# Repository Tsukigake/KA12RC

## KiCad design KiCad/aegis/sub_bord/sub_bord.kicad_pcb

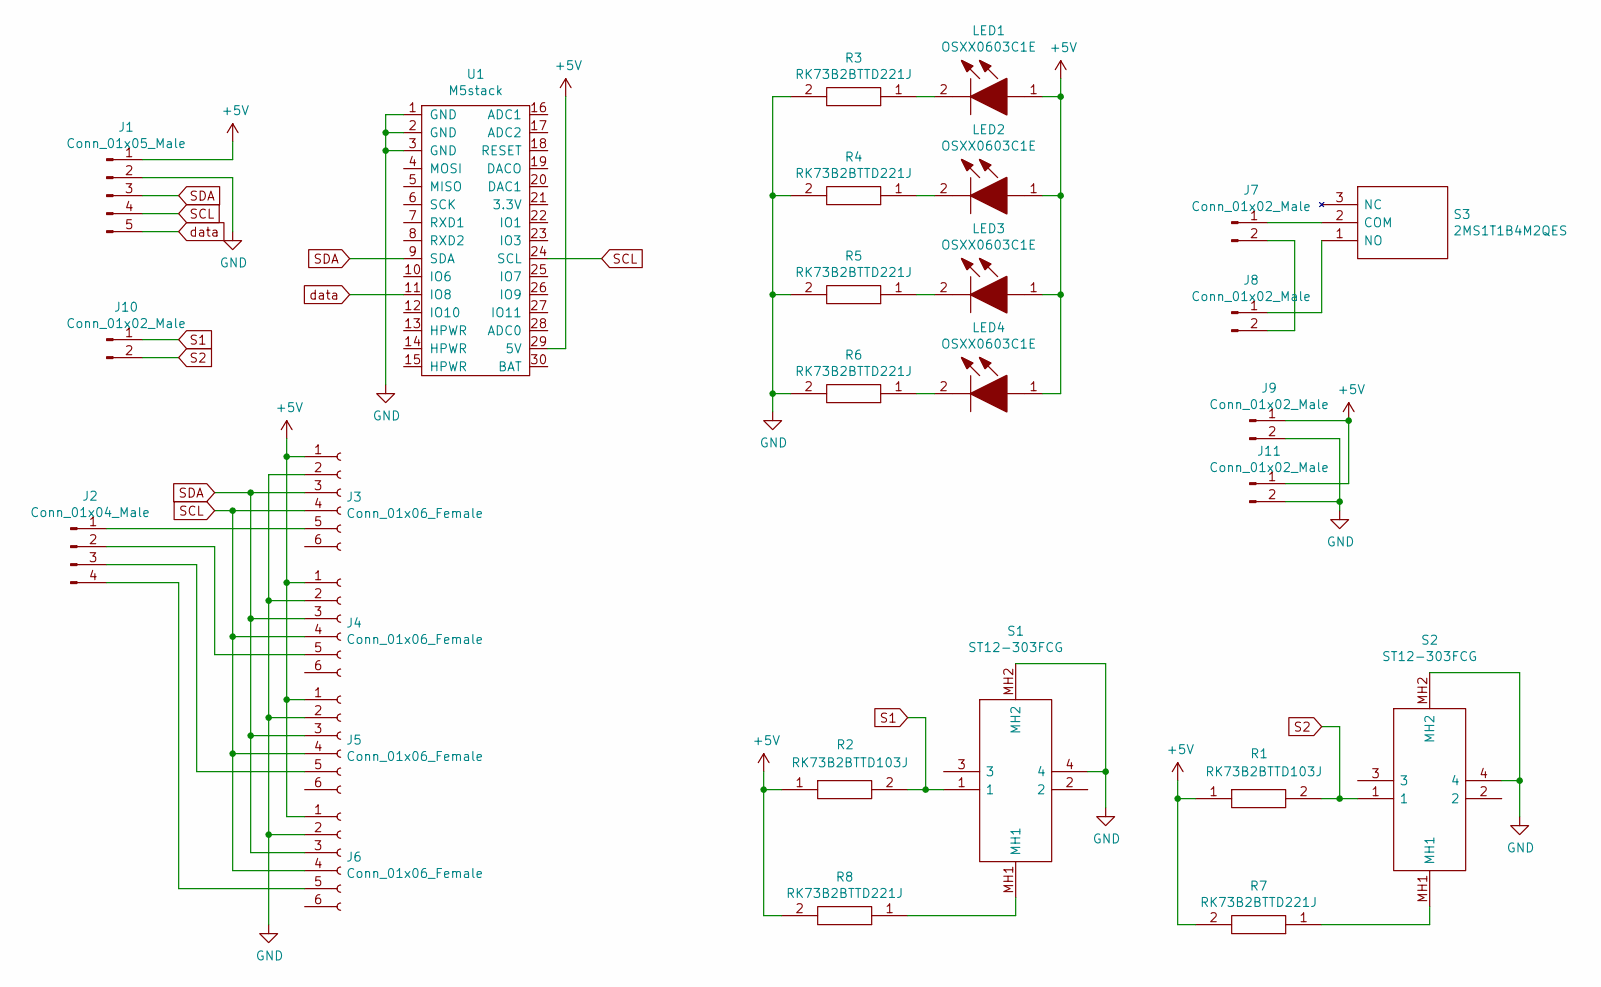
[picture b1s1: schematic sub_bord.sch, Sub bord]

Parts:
J1: Conn_01x05_Male; JST_XH_B5B-XH-A_1x05_P2.50mm_Vertical
J2: Conn_01x04_Male; JST_XH_B4B-XH-A_1x04_P2.50mm_Vertical
J3, J4, J5, J6: Conn_01x06_Female; JST_XH_B6B-XH-A_1x06_P2.50mm_Vertical
J7, J9, J10, J11: Conn_01x02_Male; JST_XH_B2B-XH-A_1x02_P2.50mm_Vertical
J8: Conn_01x02_Male; TerminalBlock_bornier-2_P5.08mm
LED1, LED2, LED3, LED4: OSXX0603C1E; Manufacturer_Part_Number OSXX0603C1E
R1, R2: RK73B2BTTD103J; RESC3216X70N; Manufacturer_Part_Number RK73B2BTTD103J
R3, R4, R5, R6, R7, R8: RK73B2BTTD221J; RESC3216X70N; Manufacturer_Part_Number RK73B2BTTD221J
S1, S2: ST12-303FCG; ST12303FCG; Manufacturer_Part_Number ST12-303FCG
S3: 2MS1T1B4M2QES; Manufacturer_Part_Number 2MS1T1B4M2QES
U1: M5stack

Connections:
+5V: J1.1, J3.1, J4.1, J5.1, J6.1, J9.1, J11.1, LED1.1, LED2.1, LED3.1, LED4.1, R1.1, R2.1, R7.2, R8.2, U1.29 (5V)
GND: J1.2, J3.2, J4.2, J5.2, J6.2, J9.2, J11.2, R3.2, R4.2, R5.2, R6.2, S1.4, S1.MH2, S2.4, S2.MH2, U1.1 (GND), U1.2 (GND), U1.3 (GND)
unnamed: J2.1, J3.5
unnamed: J2.2, J4.5
unnamed: J2.3, J5.5
unnamed: J2.4, J6.5
unnamed: J7.1, S3.2 (COM)
unnamed: J7.2, J8.2
unnamed: J8.1, S3.1 (NO)
unnamed: LED1.2, R3.1
unnamed: LED2.2, R4.1
unnamed: LED3.2, R5.1
unnamed: LED4.2, R6.1
unnamed: R7.1, S2.MH1
unnamed: R8.1, S1.MH1
S1: J10.1, R2.2, S1.1
S2: J10.2, R1.2, S2.1
SCL: J1.4, J3.4, J4.4, J5.4, J6.4, U1.24 (SCL)
SDA: J1.3, J3.3, J4.3, J5.3, J6.3, U1.9 (SDA)
data: J1.5, U1.11 (IO8)

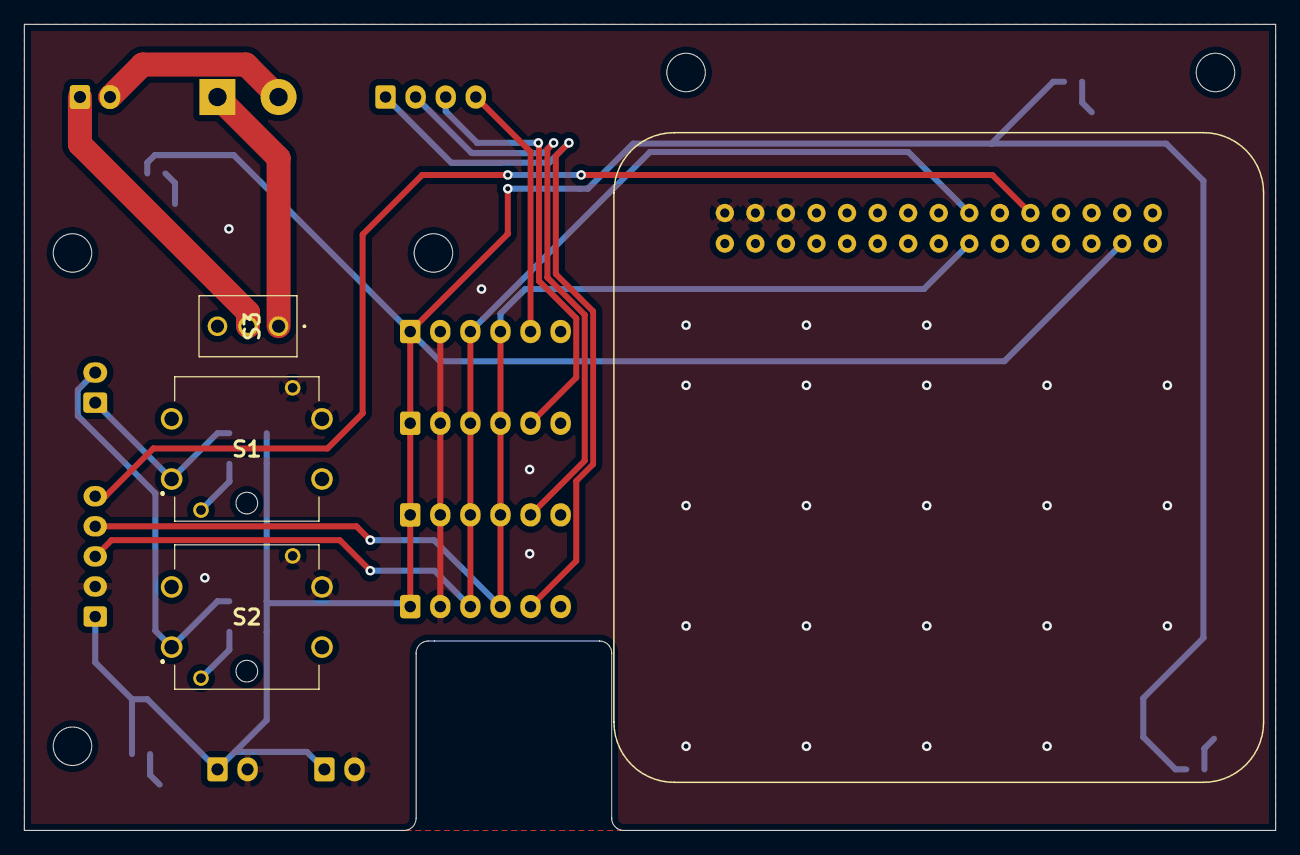
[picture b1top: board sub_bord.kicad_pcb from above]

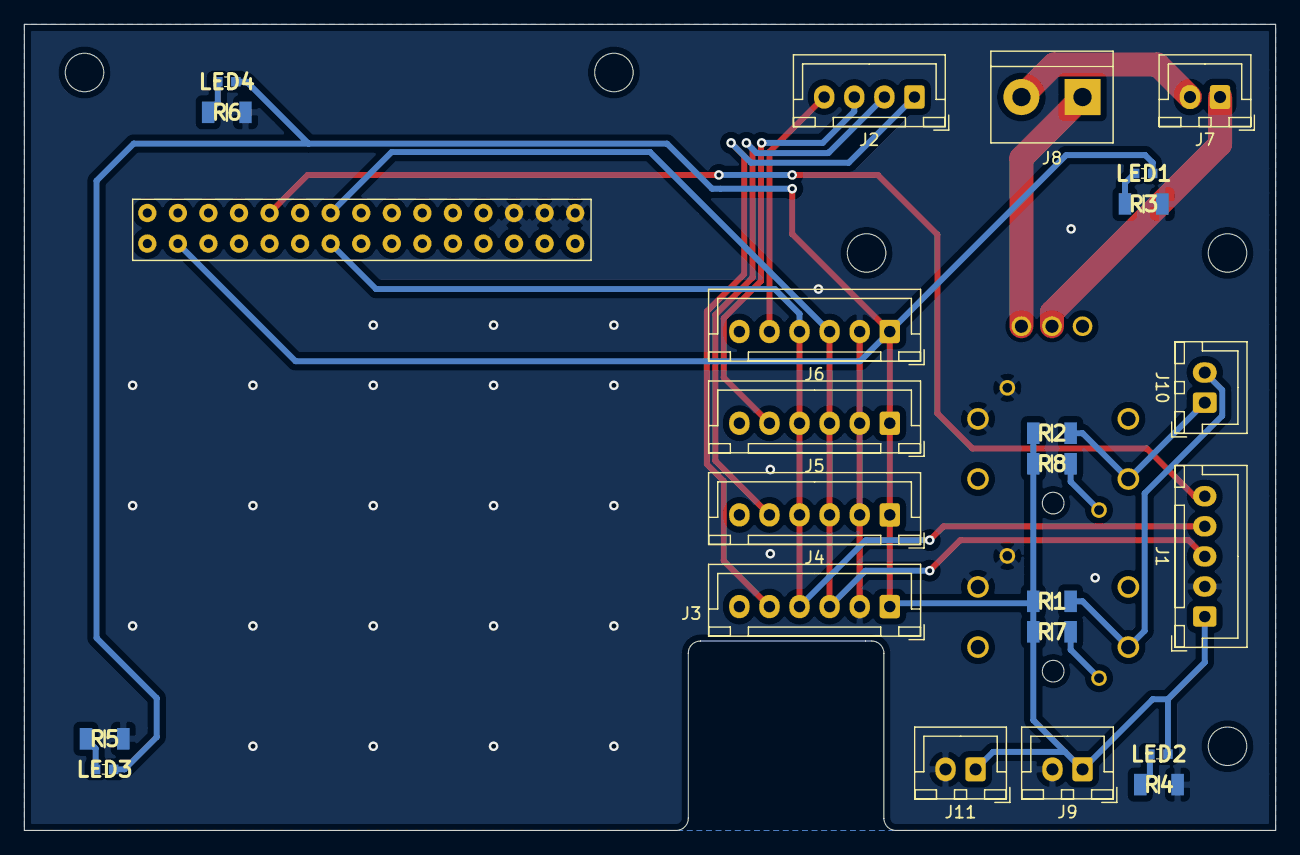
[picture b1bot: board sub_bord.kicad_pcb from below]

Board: 2 copper layers, 104.0 x 67.0 mm, 27 parts (23 on the bottom side), 20 nets.

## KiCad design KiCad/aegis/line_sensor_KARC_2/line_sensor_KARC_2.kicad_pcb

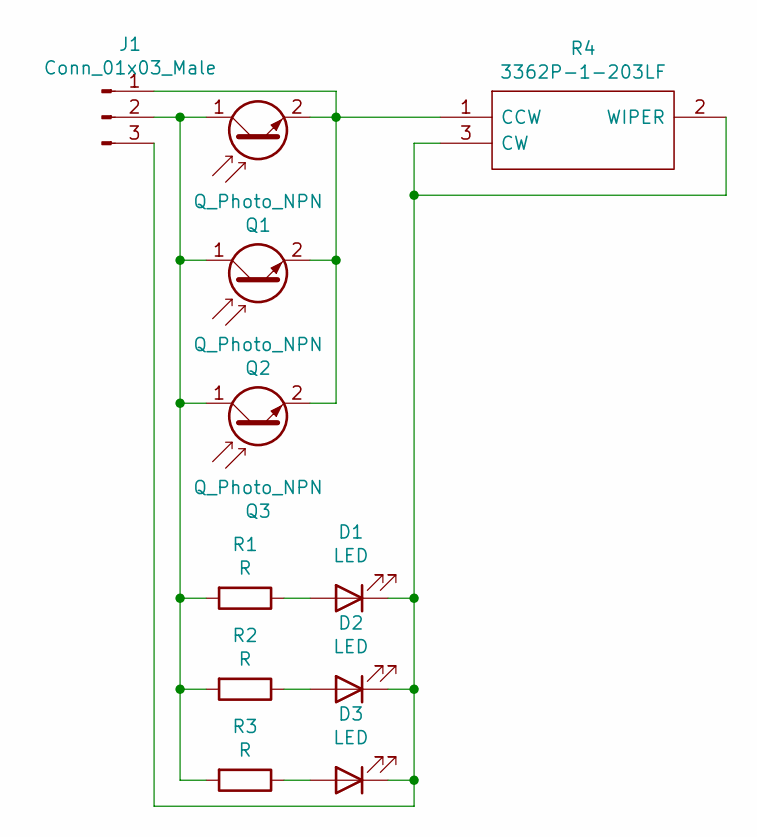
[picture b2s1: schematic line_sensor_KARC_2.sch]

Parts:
D1, D2, D3: LED; LED_D3.0mm_Clear
J1: Conn_01x03_Male; JST_XH_B3B-XH-A_1x03_P2.50mm_Vertical
Q1, Q2, Q3: Q_Photo_NPN; NJL7502L
R1, R2, R3: R; R_Axial_DIN0207_L6.3mm_D2.5mm_P7.62mm_Horizontal
R4: 3362P-1-203LF; 3362P_1; Manufacturer_Part_Number 3362P-1-203LF

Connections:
unnamed: D1.1 (K), D2.1 (K), D3.1 (K), J1.3, R4.2 (WIPER), R4.3 (CW)
unnamed: D1.2 (A), R1.1
unnamed: D2.2 (A), R2.1
unnamed: D3.2 (A), R3.1
unnamed: J1.1, Q1.2 (E), Q2.2 (E), Q3.2 (E), R4.1 (CCW)
unnamed: J1.2, Q1.1 (C), Q2.1 (C), Q3.1 (C), R1.2, R2.2, R3.2

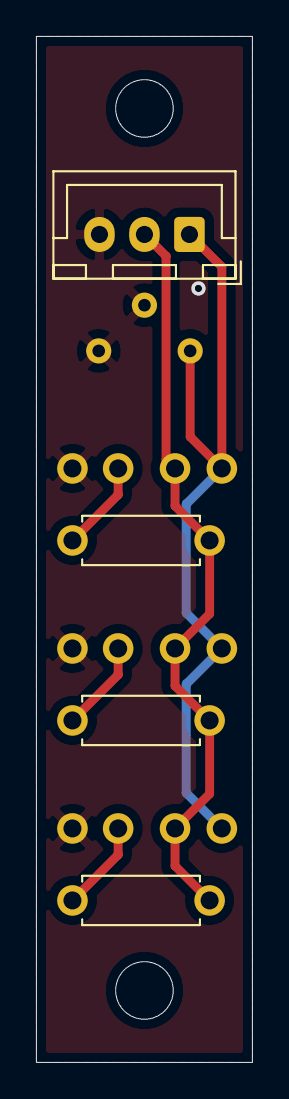
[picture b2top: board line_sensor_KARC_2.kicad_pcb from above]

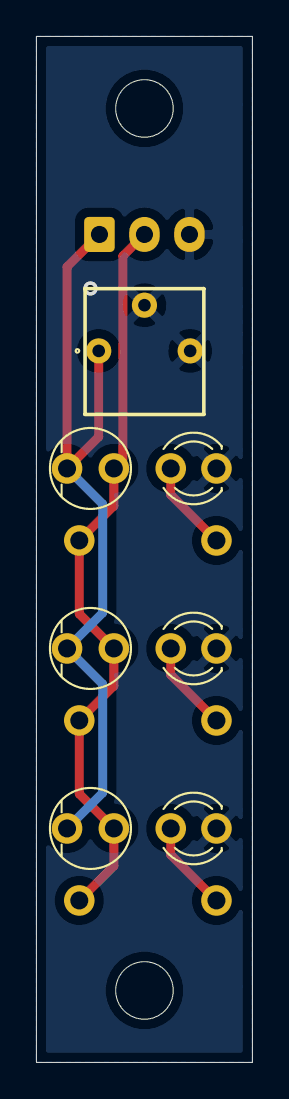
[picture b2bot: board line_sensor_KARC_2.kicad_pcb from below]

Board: 2 copper layers, 12.0 x 57.0 mm, 11 parts (7 on the bottom side), 6 nets.

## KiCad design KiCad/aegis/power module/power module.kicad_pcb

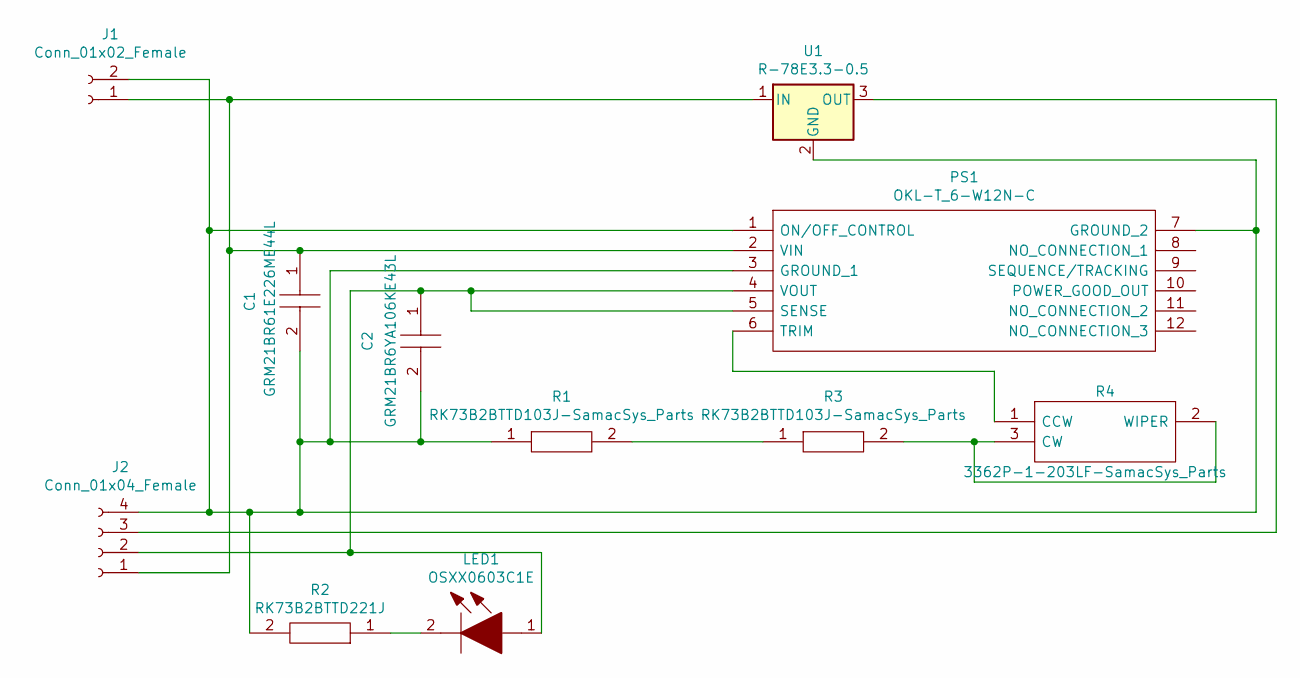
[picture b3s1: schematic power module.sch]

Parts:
C1: GRM21BR61E226ME44L; CAPC2012X145N; Manufacturer_Part_Number GRM21BR61E226ME44L
C2: GRM21BR6YA106KE43L; CAPC2012X145N; Manufacturer_Part_Number GRM21BR6YA106KE43L
J1: Conn_01x02_Female; PinHeader_1x02_P2.54mm_Vertical
J2: Conn_01x04_Female; PinHeader_1x04_P2.54mm_Vertical
LED1: OSXX0603C1E; Manufacturer_Part_Number OSXX0603C1E
PS1: OKL-T_6-W12N-C; OKLT6W12NC; Manufacturer_Part_Number OKL-T/6-W12N-C
R1, R3: RK73B2BTTD103J-SamacSys_Parts; RESC3216X70N; Manufacturer_Part_Number RK73B2BTTD103J
R2: RK73B2BTTD221J; RESC3216X70N; Manufacturer_Part_Number RK73B2BTTD221J
R4: 3362P-1-203LF-SamacSys_Parts; 3362P_1; Mouser Part Number 652-3362P-1-203LF
U1: R-78E3.3-0.5; Converter_DCDC_RECOM_R-78E-0.5_THT

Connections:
unnamed: C1.1, J1.1, J2.1, PS1.2 (VIN), U1.1 (IN)
unnamed: C1.2, C2.2, J1.2, J2.4, PS1.1 (ON/OFF_CONTROL), PS1.3 (GROUND_1), PS1.7 (GROUND_2), R1.1, R2.2, U1.2 (GND)
unnamed: C2.1, J2.2, LED1.1, PS1.4 (VOUT), PS1.5 (SENSE)
unnamed: J2.3, U1.3 (OUT)
unnamed: LED1.2, R2.1
unnamed: PS1.6 (TRIM), R4.1 (CCW)
unnamed: R1.2, R3.1
unnamed: R3.2, R4.2 (WIPER), R4.3 (CW)

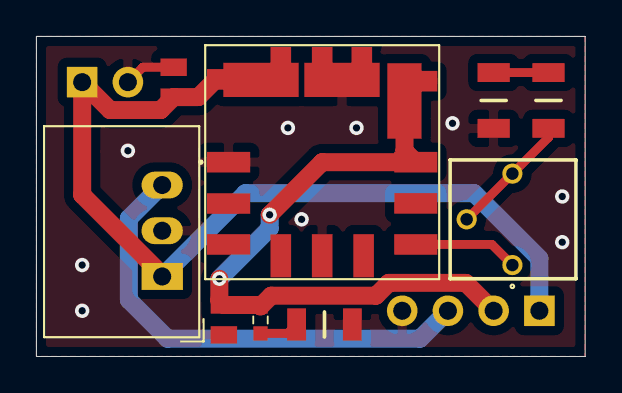
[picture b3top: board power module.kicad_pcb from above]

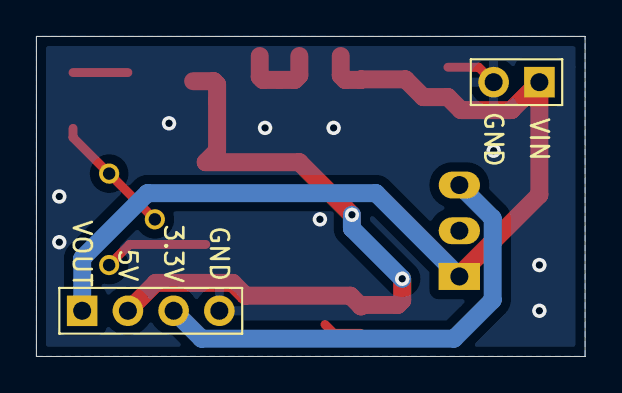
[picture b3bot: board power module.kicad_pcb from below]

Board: 2 copper layers, 30.5 x 17.8 mm, 11 parts (2 on the bottom side), 8 nets.

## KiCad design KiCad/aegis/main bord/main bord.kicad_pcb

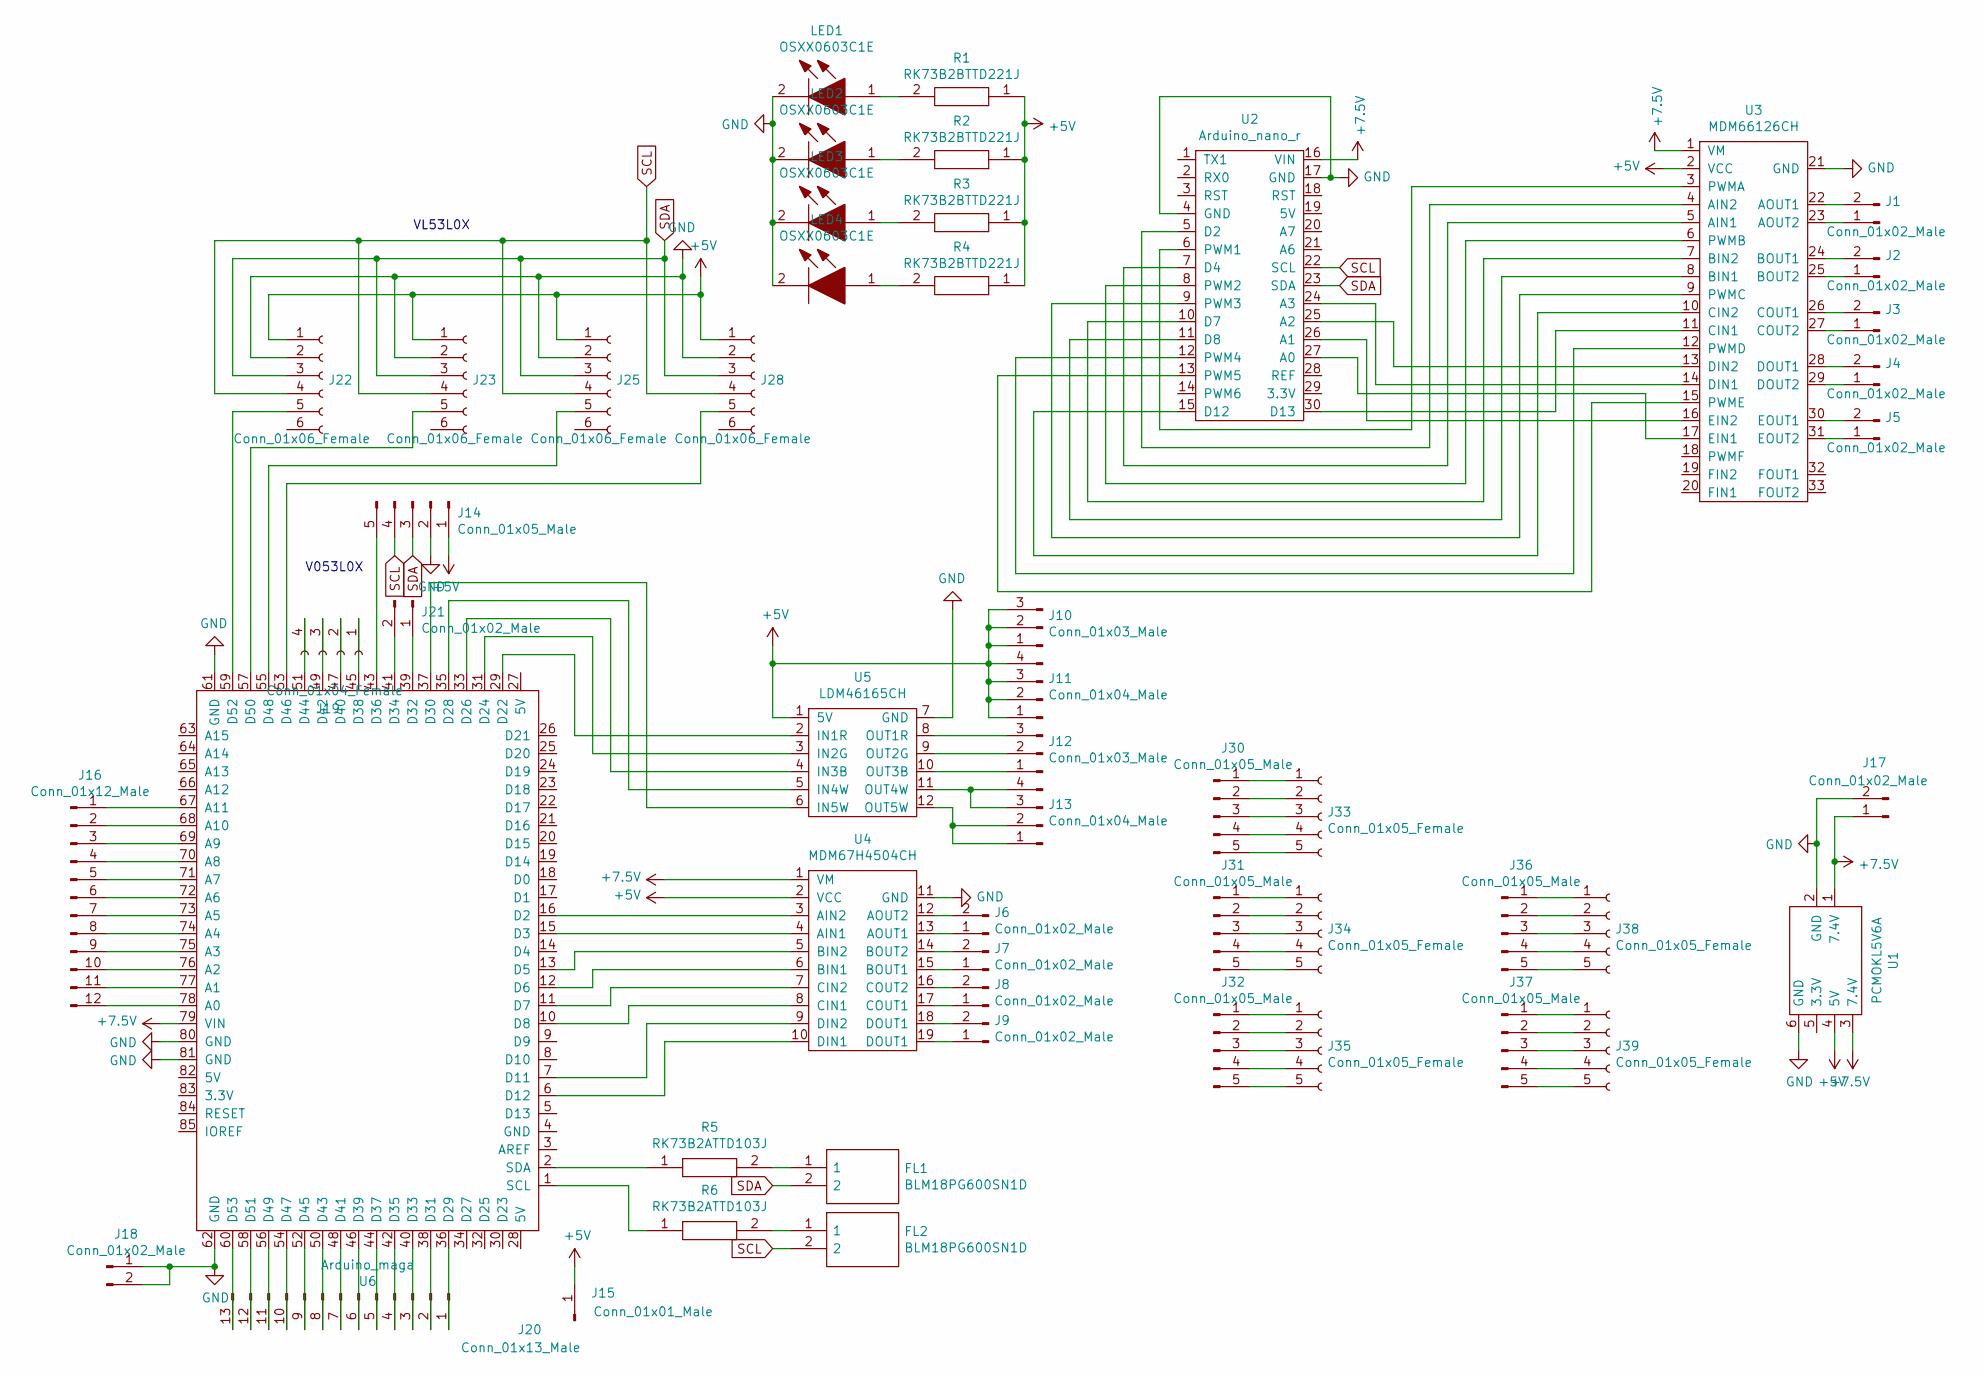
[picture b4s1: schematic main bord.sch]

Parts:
FL1, FL2: BLM18PG600SN1D; BLM18AG102BH1D; Manufacturer_Part_Number BLM18PG600SN1D
J1, J2, J3, J4, J5, J6, J7, J8, J9, J17, J21: Conn_01x02_Male; JST_XH_B2B-XH-A_1x02_P2.50mm_Vertical
J10, J12: Conn_01x03_Male; PinSocket_1x03_P2.54mm_Vertical
J11, J13: Conn_01x04_Male; PinSocket_1x04_P2.54mm_Vertical
J14: Conn_01x05_Male; JST_XH_B5B-XH-A_1x05_P2.50mm_Vertical
J15: Conn_01x01_Male; PinSocket_1x01_P2.54mm_Vertical
J16: Conn_01x12_Male; PinHeader_1x12_P2.54mm_Vertical
J18: Conn_01x02_Male; PinHeader_1x02_P2.54mm_Vertical
J19: Conn_01x04_Female; JST_XH_B4B-XH-A_1x04_P2.50mm_Vertical
J20: Conn_01x13_Male; PinHeader_1x13_P2.54mm_Vertical
J22, J23, J25, J28: Conn_01x06_Female; JST_XH_B6B-XH-A_1x06_P2.50mm_Vertical
J30, J31, J32, J36, J37: Conn_01x05_Male; PinSocket_1x05_P2.54mm_Vertical
J33, J34, J35, J38, J39: Conn_01x05_Female; PinHeader_1x05_P2.54mm_Vertical
LED1, LED2, LED3, LED4: OSXX0603C1E; Manufacturer_Part_Number OSXX0603C1E
R1, R2, R3, R4: RK73B2BTTD221J; RESC3216X70N; Manufacturer_Part_Number RK73B2BTTD221J
R5, R6: RK73B2ATTD103J; RESC2012X60N; Manufacturer_Part_Number RK73B2ATTD103J
U1: PCMOKL5V6A
U2: Arduino_nano_r
U3: MDM66126CH
U4: MDM67H4504CH
U5: LDM46165CH
U6: Arduino_maga; Arduino_mega

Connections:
+5V: J10.1, J10.2, J10.3, J11.1, J11.2, J11.3, J11.4, J14.1, J15.1, J22.1, J23.1, J25.1, J28.1, R1.1, R2.1, R3.1, R4.1, U1.4 (5V), U3.2 (VCC), U4.2 (VCC), U5.1 (5V)
+7.5V: J17.1, U1.1 (7.4V), U1.3 (7.4V), U2.16 (VIN), U3.1 (VM), U4.1 (VM), U6.79 (VIN)
GND: J14.2, J17.2, J18.1, J18.2, J22.2, J23.2, J25.2, J28.2, LED1.2, LED2.2, LED3.2, LED4.2, U1.2 (GND), U1.6 (GND), U2.4 (GND), U2.17 (GND), U3.21 (GND), U4.11 (GND), U5.7 (GND), U6.61 (GND), U6.62 (GND), U6.80 (GND), U6.81 (GND)
unnamed: FL1.1, R5.2
unnamed: FL2.1, R6.2
unnamed: J1.1, U3.23 (AOUT2)
unnamed: J1.2, U3.22 (AOUT1)
unnamed: J2.1, U3.25 (BOUT2)
unnamed: J2.2, U3.24 (BOUT1)
unnamed: J3.1, U3.27 (COUT2)
unnamed: J3.2, U3.26 (COUT1)
unnamed: J4.1, U3.29 (DOUT2)
unnamed: J4.2, U3.28 (DOUT1)
unnamed: J5.1, U3.31 (EOUT2)
unnamed: J5.2, U3.30 (EOUT1)
unnamed: J6.1, U4.13 (AOUT1)
unnamed: J6.2, U4.12 (AOUT2)
unnamed: J7.1, U4.15 (BOUT1)
unnamed: J7.2, U4.14 (BOUT2)
unnamed: J8.1, U4.17 (COUT1)
unnamed: J8.2, U4.16 (COUT2)
unnamed: J9.1, U4.19 (DOUT1)
unnamed: J9.2, U4.18 (DOUT1)
unnamed: J12.1, U5.10 (OUT3B)
unnamed: J12.2, U5.9 (OUT2G)
unnamed: J12.3, U5.8 (OUT1R)
unnamed: J13.1, J13.2, U5.12 (OUT5W)
unnamed: J13.3, J13.4, U5.11 (OUT4W)
unnamed: J14.5, U6.43 (D36)
unnamed: J16.1, U6.67 (A11)
unnamed: J16.2, U6.68 (A10)
unnamed: J16.3, U6.69 (A9)
unnamed: J16.4, U6.70 (A8)
unnamed: J16.5, U6.71 (A7)
unnamed: J16.6, U6.72 (A6)
unnamed: J16.7, U6.73 (A5)
unnamed: J16.8, U6.74 (A4)
unnamed: J16.9, U6.75 (A3)
unnamed: J16.10, U6.76 (A2)
unnamed: J16.11, U6.77 (A1)
unnamed: J16.12, U6.78 (A0)
unnamed: J19.1, U6.45 (D38)
unnamed: J19.2, U6.47 (D40)
unnamed: J19.3, U6.49 (D42)
unnamed: J19.4, U6.51 (D44)
unnamed: J20.1, U6.36 (D29)
unnamed: J20.2, U6.38 (D31)
unnamed: J20.3, U6.40 (D33)
unnamed: J20.4, U6.42 (D35)
unnamed: J20.5, U6.44 (D37)
unnamed: J20.6, U6.46 (D39)
unnamed: J20.7, U6.48 (D41)
unnamed: J20.8, U6.50 (D43)
unnamed: J20.9, U6.52 (D45)
unnamed: J20.10, U6.54 (D47)
unnamed: J20.11, U6.56 (D49)
unnamed: J20.12, U6.58 (D51)
unnamed: J20.13, U6.60 (D53)
unnamed: J21.1, U6.39 (D32)
unnamed: J21.2, U6.41 (D34)
unnamed: J22.5, U6.59 (D52)
unnamed: J23.5, U6.57 (D50)
unnamed: J25.5, U6.55 (D48)
unnamed: J28.5, U6.53 (D46)
unnamed: J30.1, J33.1
unnamed: J30.2, J33.2
unnamed: J30.3, J33.3
unnamed: J30.4, J33.4
unnamed: J30.5, J33.5
unnamed: J31.1, J34.1
unnamed: J31.2, J34.2
unnamed: J31.3, J34.3
unnamed: J31.4, J34.4
unnamed: J31.5, J34.5
unnamed: J32.1, J35.1
unnamed: J32.2, J35.2
unnamed: J32.3, J35.3
unnamed: J32.4, J35.4
unnamed: J32.5, J35.5
unnamed: J36.1, J38.1
unnamed: J36.2, J38.2
unnamed: J36.3, J38.3
unnamed: J36.4, J38.4
unnamed: J36.5, J38.5
unnamed: J37.1, J39.1
unnamed: J37.2, J39.2
unnamed: J37.3, J39.3
unnamed: J37.4, J39.4
unnamed: J37.5, J39.5
unnamed: LED1.1, R1.2
unnamed: LED2.1, R2.2
unnamed: LED3.1, R3.2
unnamed: LED4.1, R4.2
unnamed: R5.1, U6.2 (SDA)
unnamed: R6.1, U6.1 (SCL)
unnamed: U2.5 (D2), U3.4 (AIN2)
unnamed: U2.6 (PWM1), U3.3 (PWMA)
unnamed: U2.7 (D4), U3.5 (AIN1)
unnamed: U2.8 (PWM2), U3.6 (PWMB)
unnamed: U2.9 (PWM3), U3.9 (PWMC)
unnamed: U2.10 (D7), U3.7 (BIN2)
unnamed: U2.11 (D8), U3.8 (BIN1)
unnamed: U2.12 (PWM4), U3.12 (PWMD)
unnamed: U2.13 (PWM5), U3.15 (PWME)
unnamed: U2.15 (D12), U3.10 (CIN2)
unnamed: U2.24 (A3), U3.14 (DIN1)
unnamed: U2.25 (A2), U3.13 (DIN2)
unnamed: U2.26 (A1), U3.16 (EIN2)
unnamed: U2.27 (A0), U3.17 (EIN1)
unnamed: U2.30 (D13), U3.11 (CIN1)
unnamed: U4.3 (AIN2), U6.16 (D2)
unnamed: U4.4 (AIN1), U6.15 (D3)
unnamed: U4.5 (BIN2), U6.13 (D5)
unnamed: U4.6 (BIN1), U6.12 (D6)
unnamed: U4.7 (CIN2), U6.11 (D7)
unnamed: U4.8 (CIN1), U6.10 (D8)
unnamed: U4.9 (DIN2), U6.7 (D11)
unnamed: U4.10 (DIN1), U6.6 (D12)
unnamed: U5.2 (IN1R), U6.29 (D22)
unnamed: U5.3 (IN2G), U6.31 (D24)
unnamed: U5.4 (IN3B), U6.33 (D26)
unnamed: U5.5 (IN4W), U6.35 (D28)
unnamed: U5.6 (IN5W), U6.37 (D30)
SCL: FL2.2, J14.4, J22.4, J23.4, J25.4, J28.4, U2.22 (SCL)
SDA: FL1.2, J14.3, J22.3, J23.3, J25.3, J28.3, U2.23 (SDA)

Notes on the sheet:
VL53L0X
V053L0X

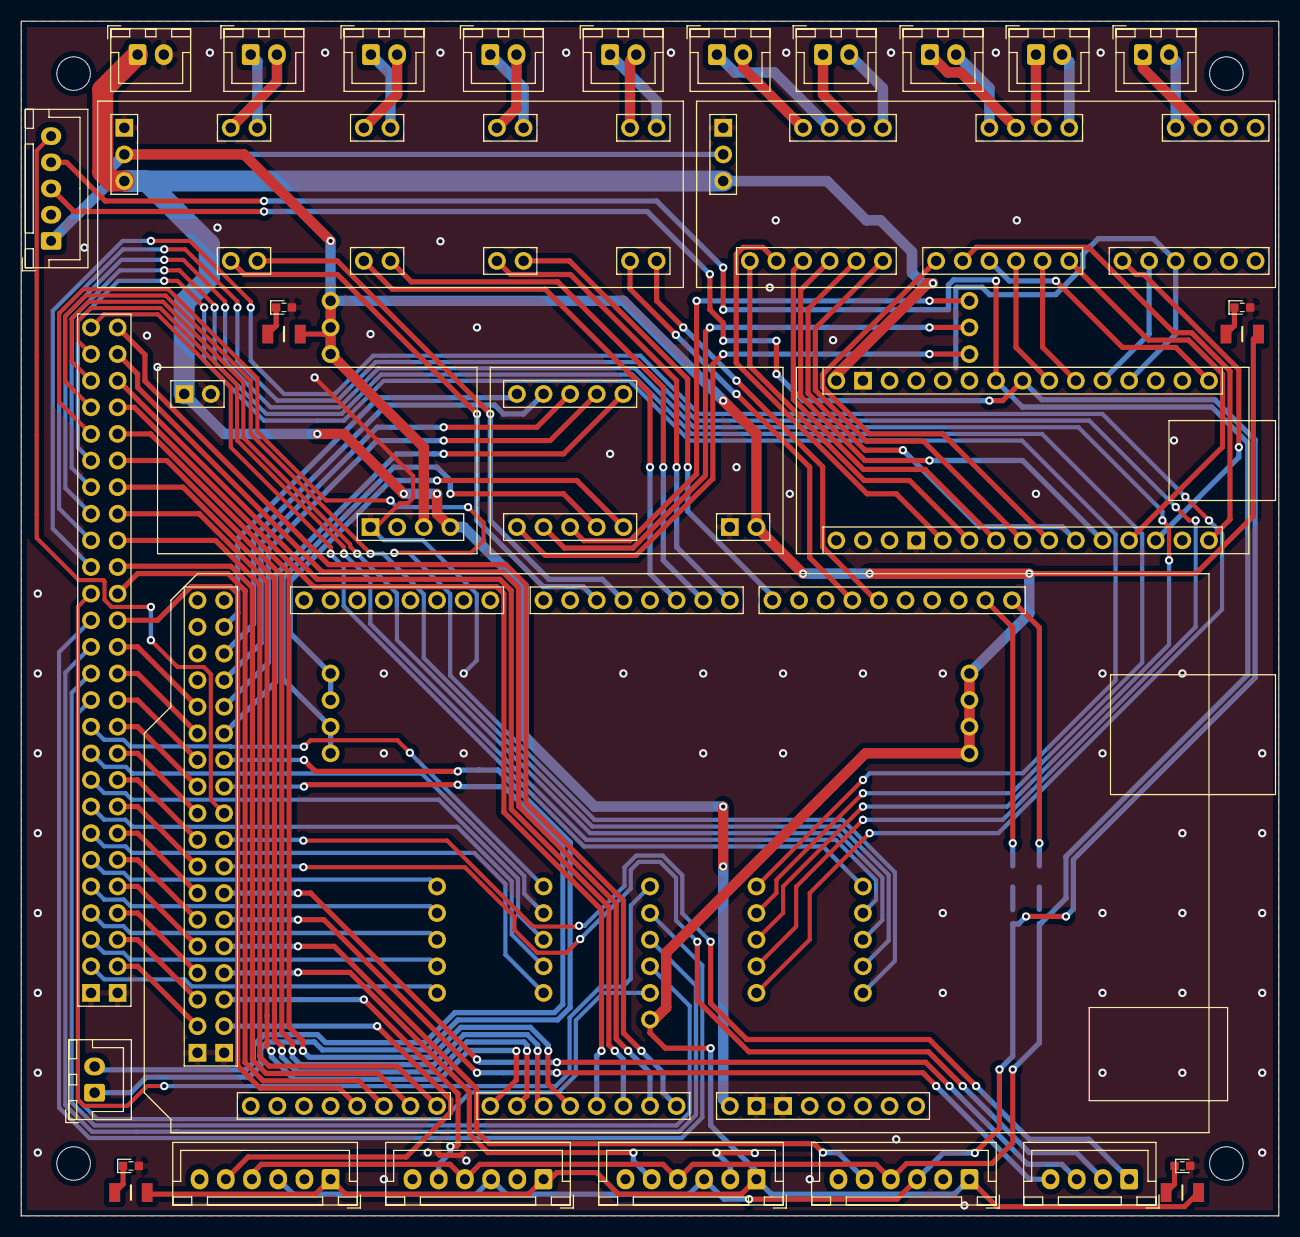
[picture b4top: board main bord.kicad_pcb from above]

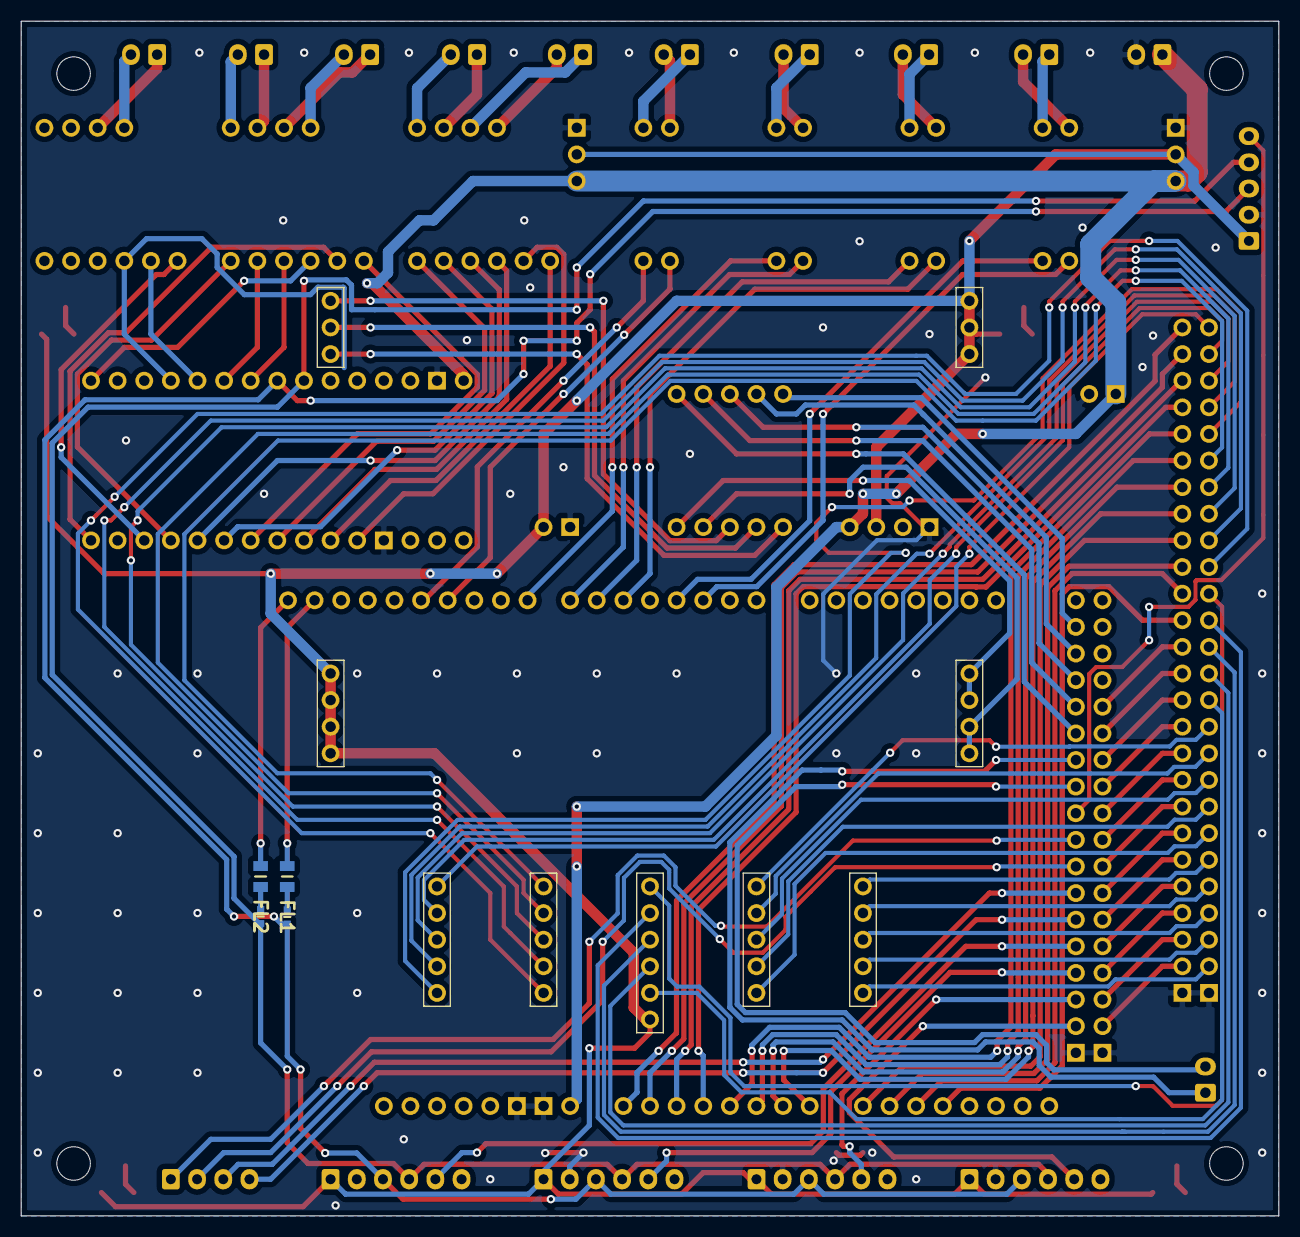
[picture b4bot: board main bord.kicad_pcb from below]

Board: 2 copper layers, 120.0 x 114.0 mm, 53 parts (14 on the bottom side), 125 nets.

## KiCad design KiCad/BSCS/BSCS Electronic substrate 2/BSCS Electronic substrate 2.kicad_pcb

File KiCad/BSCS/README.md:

# Bidirectional_Serial_Communication_System

kamiokanndeです！

ロボカップジュニアレスキュー部門に参加している「爪を隠した鷹」のハード、ソフト、基盤（要するに全部）担当です。

このKiCadデータはロボット部内向けに公開したものでありますので、読みにくいところがあると思いますがご承知おきください。

本リポジトリに掲載されているハードウエア、ソフトウエアおよびシステムに関する情報等の掲載内容は、技術の進歩などにより予告なしに変更されることがあります。

また、上記資料などに記載のデータ、図、表などに示す技術的な内容、プログラム、アルゴリズムその他応用回路例などの情報を使用する場合は、使用者のシステム全体で十分に評価し、使用者の責任において適用可否をご判断ください。

また、このデータを複製、改変しロボットに搭載することによって生じた不具合及び故障についての責任を負いません。

こんなことはないと思いますが、 本製品、または本資料に掲載されている技術情報を、大量破壊兵器の開発等の目的、軍事利用の目的、あるいはその他軍事用途の目的で使用しないでください。

ご質問などは https://twitter.com/kamiokannde1 までDMをしていただけたら幸いです。

Kaiyo Academy Robot Club Rescue Department Manager (2021)

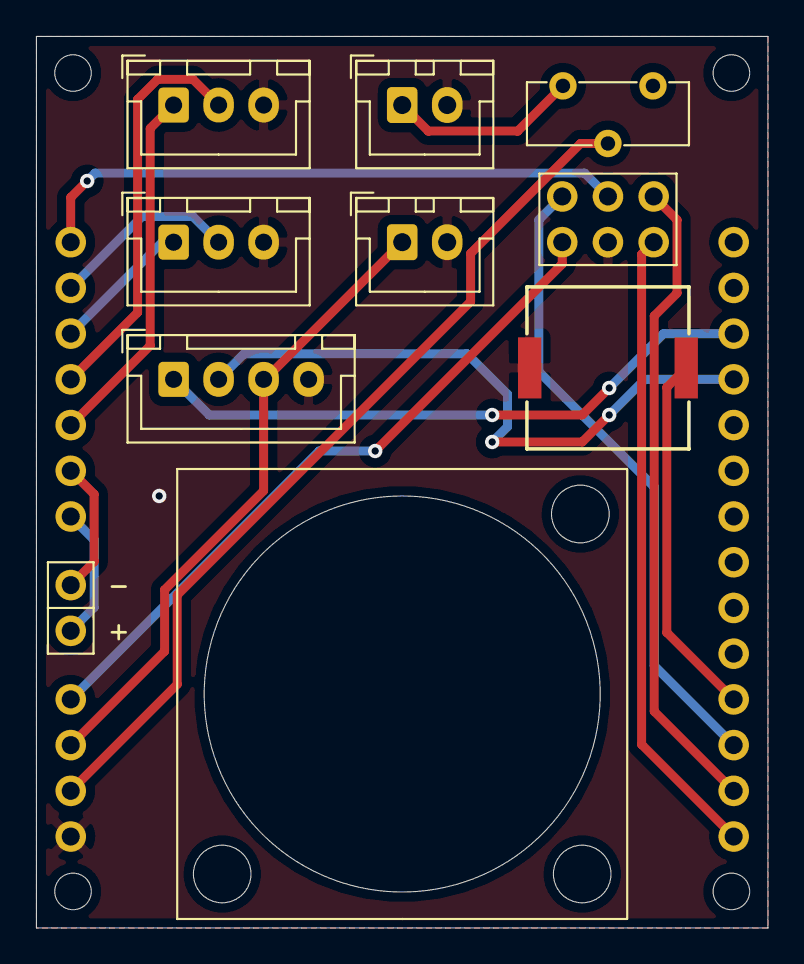
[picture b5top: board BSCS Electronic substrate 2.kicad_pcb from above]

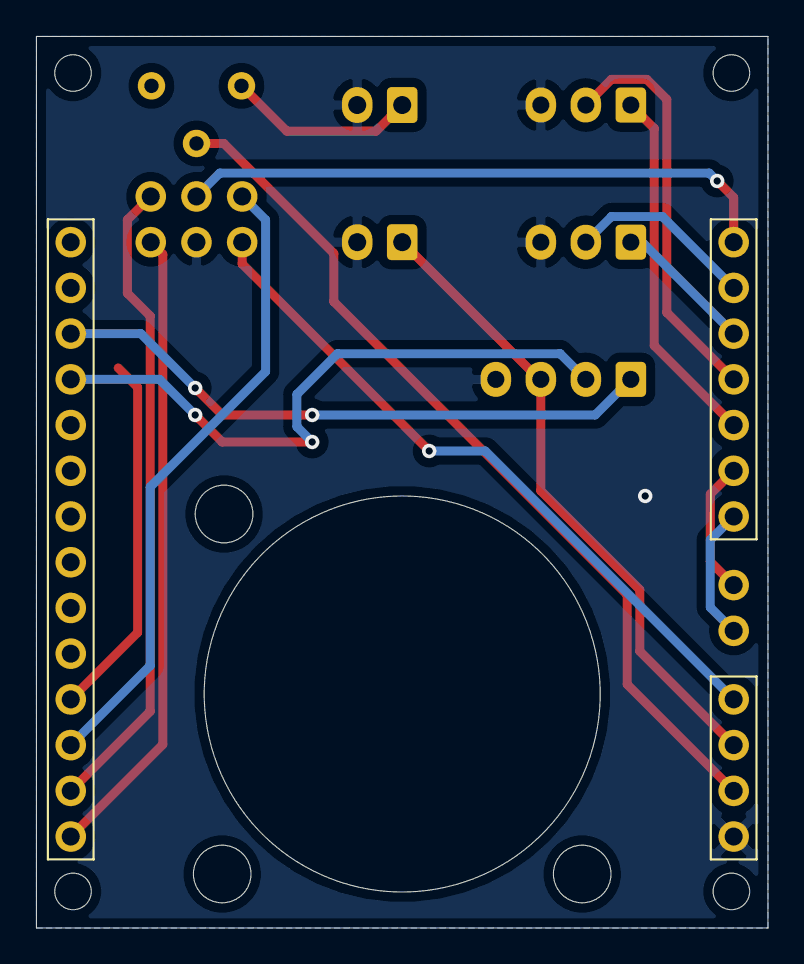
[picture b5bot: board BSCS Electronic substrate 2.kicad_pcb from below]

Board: 2 copper layers, 40.6 x 49.5 mm, 12 parts (3 on the bottom side), 18 nets.

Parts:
J1: Conn_01x14_Male; PinSocket_1x14_P2.54mm_Vertical
J2: Conn_01x07_Male; PinSocket_1x07_P2.54mm_Vertical
J3: Conn_01x04_Male; PinSocket_1x04_P2.54mm_Vertical
J4, J5: Conn_01x03_Female; JST_XH_B3B-XH-A_1x03_P2.50mm_Vertical
J6, J8: Conn_01x02_Female; JST_XH_B2B-XH-A_1x02_P2.50mm_Vertical
J7: Conn_01x02_Female; PinHeader_1x02_P2.54mm_Vertical
J9: Conn_01x04_Female; JST_XH_B4B-XH-A_1x04_P2.50mm_Vertical
J10: Conn_02x03_Counter_Clockwise; PinHeader_2x03_P2.54mm_Vertical
LS1: PKMCS0909E4000-R1; PKMCS
S1: 2MS1T1B4M2QES; IS-1235-G

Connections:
5VD: J3.3, J8.1, J9.3
5V_USBSERIAL: J3.4, J10.6
A2: J1.3, J9.1
A3: J1.4, J9.2
D10: J1.11, LS1.1
D11: J1.12, J10.5
D12: J1.13, J10.1
D13: J1.14, J10.2
GND: J3.1, J4.3, J5.3, J6.2, J8.2, J9.4, J10.4, LS1.2
MO1: J2.6, J7.1
MO2: J2.7, J7.2
unnamed: J6.1, S1.1
RESET: J2.1, J10.3
RX: J2.2, J5.2
SCL: J2.4, J4.2
SDA: J2.5, J4.1
TX: J2.3, J5.1
VCC: J3.2, S1.2
